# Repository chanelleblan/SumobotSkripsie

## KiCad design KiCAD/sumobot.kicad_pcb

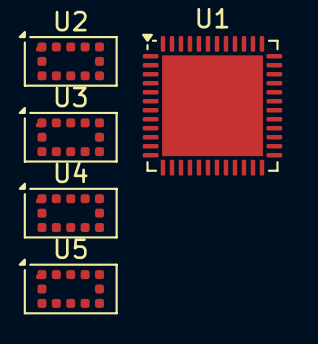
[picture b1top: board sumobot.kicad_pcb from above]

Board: 2 copper layers, 5 parts (0 on the bottom side), 5 nets, no tracks yet.

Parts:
U1: STM32F411CEUx; QFN-48-1EP_7x7mm_P0.5mm_EP5.6x5.6mm
U2, U3, U4, U5: VL53L0CXV0DH1; ST_VL53L1x

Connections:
unnamed: U1.23 (VSS), U1.35 (VSS), U1.47 (VSS), U1.49 (VSS)
unnamed: U2.3 (GND), U2.4 (GND), U2.6 (GND), U2.12 (GND)
unnamed: U3.3 (GND), U3.4 (GND), U3.6 (GND), U3.12 (GND)
unnamed: U4.3 (GND), U4.4 (GND), U4.6 (GND), U4.12 (GND)
unnamed: U5.3 (GND), U5.4 (GND), U5.6 (GND), U5.12 (GND)
